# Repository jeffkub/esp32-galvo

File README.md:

# esp32-galvo
Laser galvo controller board using the ESP32.

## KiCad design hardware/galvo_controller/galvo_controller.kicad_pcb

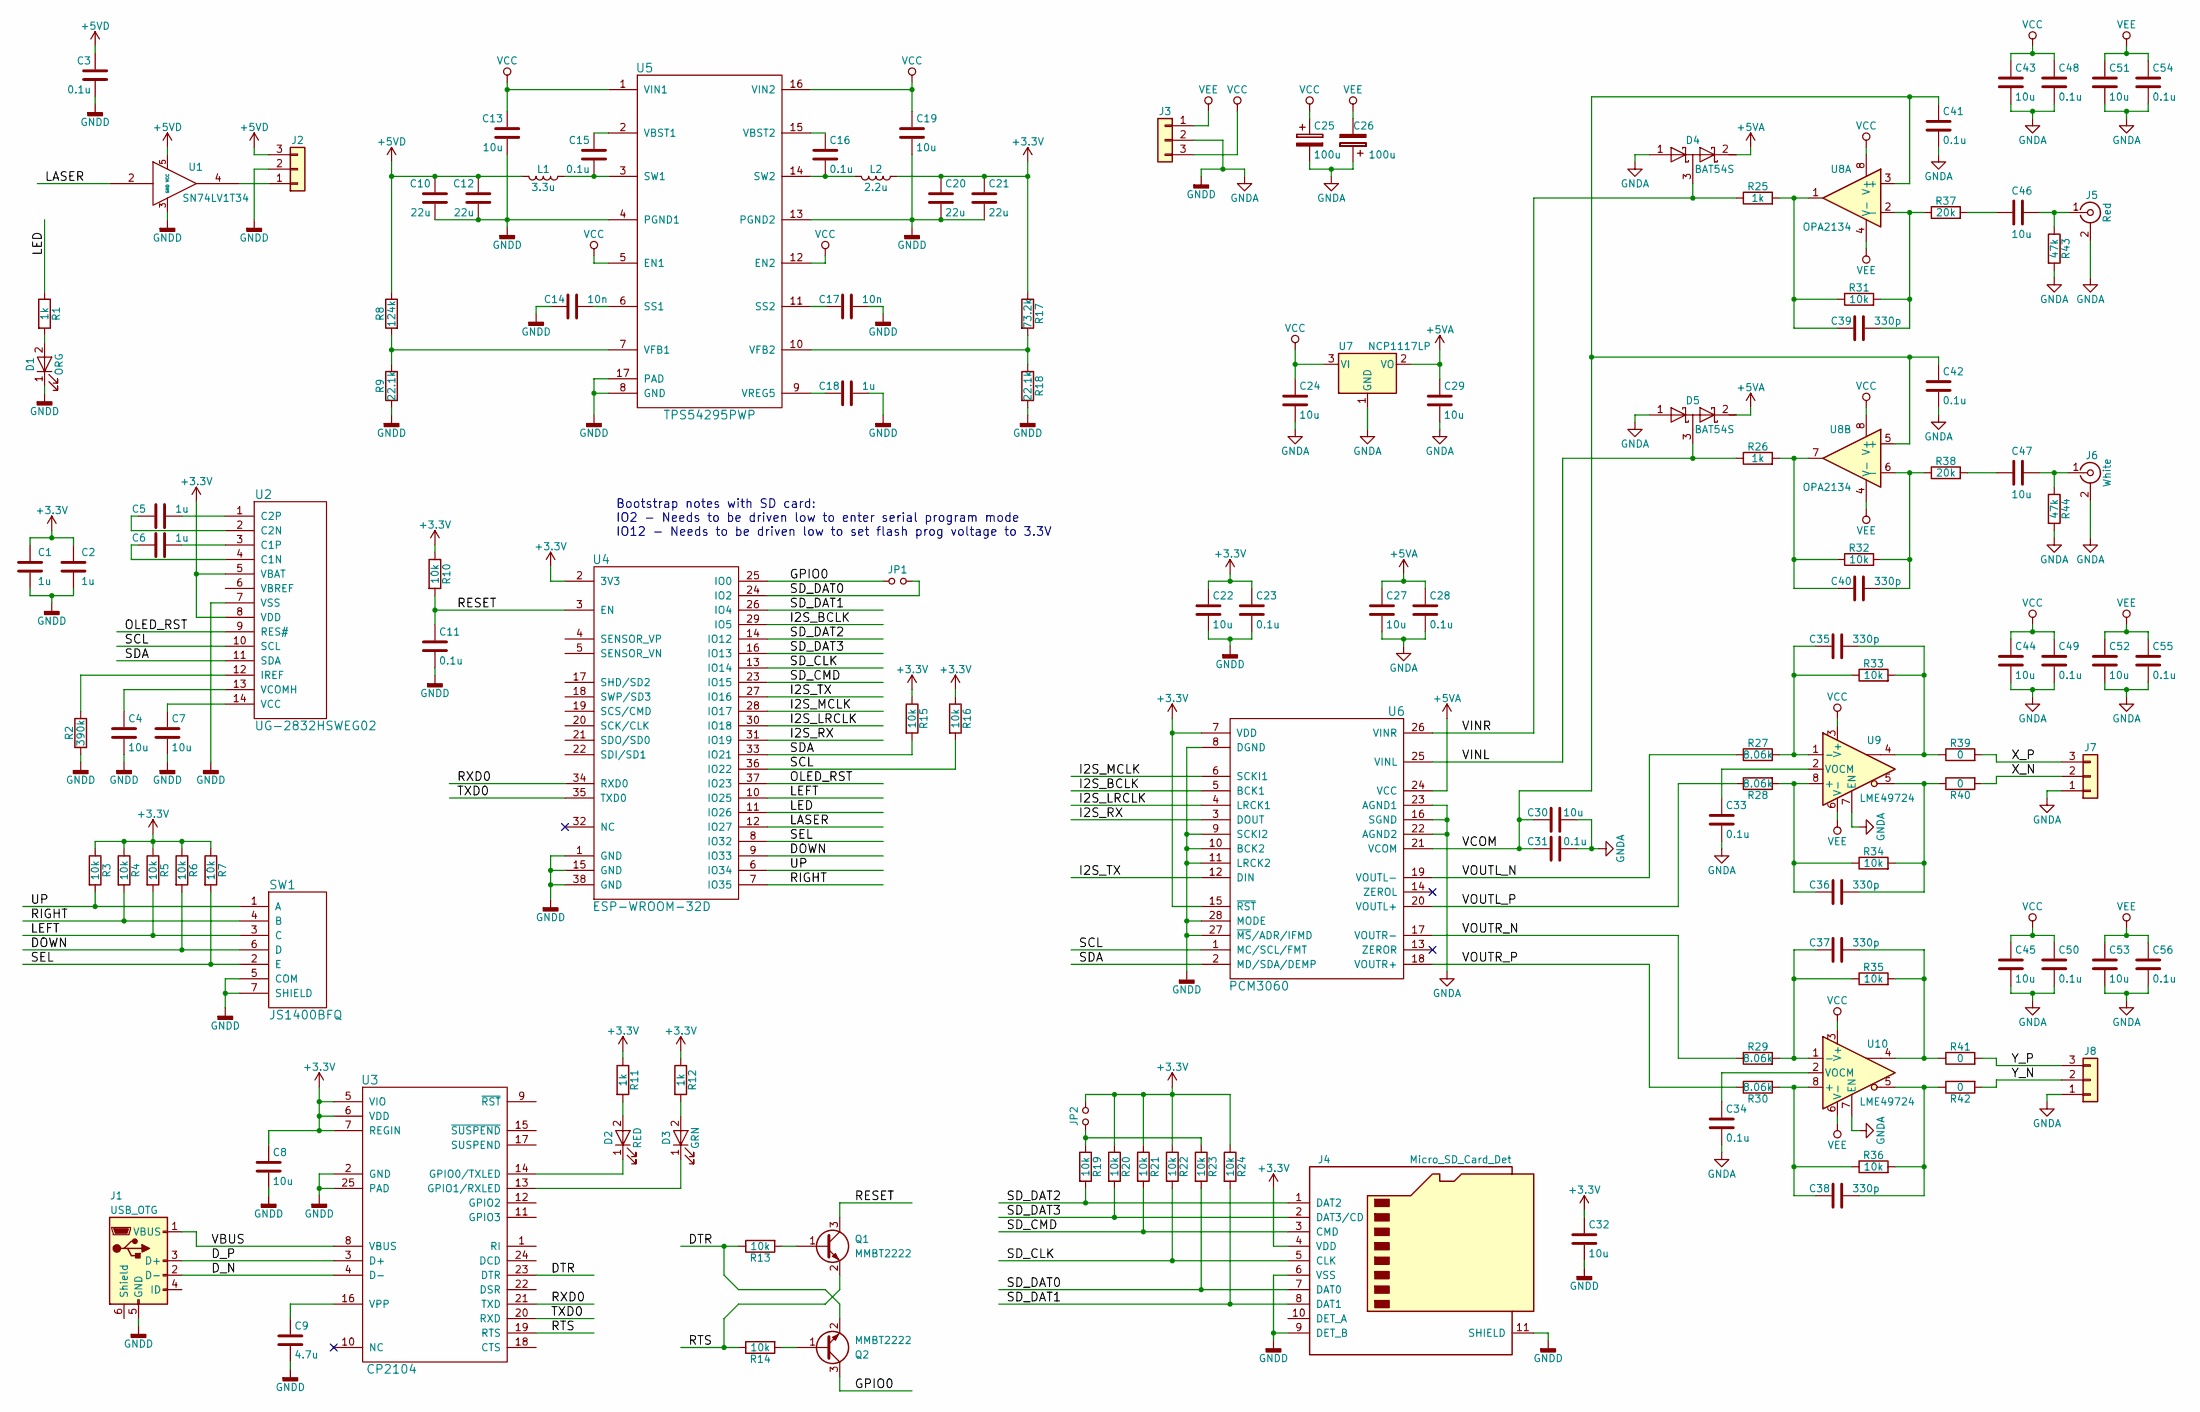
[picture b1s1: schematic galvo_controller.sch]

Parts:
C1, C2, C5, C6, C18: 1u; C_0805; Part 490-1691-1-ND
C3, C11, C15, C16, C23, C28, C31, C33, C34, C41, C42, C48, C49, C50, C54, C55, C56: 0.1u; C_0603; Part 490-9691-1-ND
C4, C7, C8, C13, C19, C22, C24, C27, C29, C30, C32, C43, C44, C45, C46, C47, C51, C52, C53: 10u; C_0805; Part 490-5523-1-ND
C9: 4.7u; C_0805; Part 490-5422-1-ND
C10, C12, C20, C21: 22u; C_1206; Part 490-6509-1-ND
C14, C17: 10n; C_0603; Part 490-9734-1-ND
C25, C26: 100u; CP_Elec_6.3x7.7; Part PCE3951CT-ND
C35, C36, C37, C38, C39, C40: 330p; C_0603; Part 490-11460-1-ND
D1: ORG; D_0603; Part 160-1434-1-ND
D2: RED; D_0603; Part 160-1447-1-ND
D3: GRN; D_0603; Part 160-1435-1-ND
D4, D5: BAT54S; SOT-23; Part BAT54S-FDICT-ND
J1: USB_OTG; 10118192; Part 609-4613-1-ND
J2, J7, J8: Conn_01x03; JST_XH_B03B-XH-A_03x2.50mm_Straight; Part 455-2248-ND
J3: Conn_01x03; Molex_KK-6410-03_03x2.54mm_Straight; Part WM4201-ND
J4: Micro_SD_Card_Det; 503182-1853; Part WM9750CT-ND
J5: Red; RCJ-01x; Part CP-1401-ND
J6: White; RCJ-01x; Part CP-1402-ND
JP1, JP2: Jumper_NO_Small; Pin_Header_Straight_1x02_Pitch2.54mm; Part 3M9457-02-ND
L1: 3.3u; CLF7045-D; Part 445-9554-1-ND
L2: 2.2u; CLF7045-D; Part 445-9553-1-ND
Q1, Q2: MMBT2222; SOT-23; Part MMBT2222ALT3GOSCT-ND
R1, R11, R12, R25, R26: 1k; R_0603; Part 311-1.00KHRCT-ND
R2: 390k; R_0603; Part 311-390KHRCT-ND
R3, R4, R5, R6, R7, R10, R13, R14, R15, R16, R19, R20, R21, R22, R23, R24, R31, R32, R33, R34, R35, R36: 10k; R_0603; Part 311-10.0KHRCT-ND
R8: 124k; R_0603; Part 311-124KHRCT-ND
R9, R18: 22.1k; R_0603; Part 311-22.1KHRCT-ND
R17: 73.2k; R_0603; Part 311-73.2KHRCT-ND
R27, R28, R29, R30: 8.06k; R_0603; Part 311-8.06KHRCT-ND
R37, R38: 20k; R_0603; Part 311-20.0KHRCT-ND
R39, R40, R41, R42: 0; R_0603; Part 311-0.0GRCT-ND
R43, R44: 47k; R_0603; Part 311-47.0KHRCT-ND
SW1: JS1400BFQ; Part 612-JS1400BFQ
U1: SN74LV1T34; SOT-23-5; Part 296-37176-1-ND
U2: UG-2832HSWEG02; Part UG-2832HSWEG02
U3: CP2104; QFN-24-1EP_4x4mm_Pitch0.5mm; Part 336-2008-5-ND
U4: ESP-WROOM-32D; ESP32-WROOM; Part 1528-1801-ND
U5: TPS54295PWP; HTSSOP-16-1EP_4.4x5mm_Pitch0.65mm_ThermalVias; Part 296-29960-1-ND
U6: PCM3060
U7: NCP1117LP; SOT-223-3_TabPin2; Part NCP1117LPST50T3GOSCT-ND
U8: OPA2134; SOIC-8_3.9x4.9mm_Pitch1.27mm; Part 296-22024-1-ND
U9, U10: LME49724; SOIC-8-1EP_3.9x4.9mm_Pitch1.27mm; Part 296-37390-1-ND

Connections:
+3V3: C1.2, C2.2, C8.1, C20.1, C21.1, C22.1, C23.1, C32.1, J4.4 (VDD), JP2.2, L2.1, R3.1, R4.1, R5.1, R6.1, R7.1, R10.1, R11.1, R12.1, R15.1, R16.1, R17.1, R20.1, R21.1, R22.1, R24.1, U2.5 (VBAT), U2.8 (VDD), U3.5 (VIO), U3.6 (VDD), U3.7 (REGIN), U4.2 (3V3), U6.7 (VDD), U6.15 (~RST)
+5VA: C27.1, C28.1, C29.1, D4.2 (K), D5.2 (K), U6.24 (VCC), U7.2 (VO)
+5VD: C3.1, C10.1, C12.1, J2.3, L1.2, R8.1, U1.5 (VCC)
/DOWN: R6.2, SW1.6 (D), U4.9 (IO33)
/DTR: Q2.2 (E), R13.1, U3.23 (DTR)
/D_N: J1.2 (D-), U3.4 (D-)
/D_P: J1.3 (D+), U3.3 (D+)
/GPIO0: JP1.1, Q2.3 (C), U4.25 (IO0)
/I2S_BCLK: U4.29 (IO5), U6.5 (BCK1)
/I2S_LRCLK: U4.30 (IO18), U6.4 (LRCK1)
/I2S_MCLK: U4.28 (IO17), U6.6 (SCKI1)
/I2S_RX: U4.31 (IO19), U6.3 (DOUT)
/I2S_TX: U4.27 (IO16), U6.12 (DIN)
/LASER: U1.2, U4.12 (IO27)
/LED: R1.1, U4.11 (IO26)
/LEFT: R5.2, SW1.3 (C), U4.10 (IO25)
/OLED_RST: U2.9 (RES#), U4.37 (IO23)
/RESET: C11.1, Q1.3 (C), R10.2, U4.3 (EN)
/RIGHT: R4.2, SW1.4 (B), U4.7 (IO35)
/RTS: Q1.2 (E), R14.1, U3.19 (RTS)
/RXD0: U3.21 (TXD), U4.34 (RXD0)
/SCL: R16.2, U2.10 (SCL), U4.36 (IO22), U6.1 (MC/SCL/FMT)
/SDA: R15.2, U2.11 (SDA), U4.33 (IO21), U6.2 (MD/SDA/DEMP)
/SD_CLK: J4.5 (CLK), R22.2, U4.13 (IO14)
/SD_CMD: J4.3 (CMD), R21.2, U4.23 (IO15)
/SD_DAT0: J4.7 (DAT0), JP1.2, R23.2, U4.24 (IO2)
/SD_DAT1: J4.8 (DAT1), R24.2, U4.26 (IO4)
/SD_DAT2: J4.1 (DAT2), R19.2, U4.14 (IO12)
/SD_DAT3: J4.2 (DAT3/CD), R20.2, U4.16 (IO13)
/SEL: R7.2, SW1.2 (E), U4.8 (IO32)
/TXD0: U3.20 (RXD), U4.35 (TXD0)
/UP: R3.2, SW1.1 (A), U4.6 (IO34)
/VBUS: J1.1 (VBUS), U3.8 (VBUS)
/VCOM: C30.2, C31.2, C41.1, C42.1, U6.21 (VCOM), U8.3 (+), U8.5 (+)
/VINL: D5.3 (common), R26.1, U6.25 (VINL)
/VINR: D4.3 (common), R25.1, U6.26 (VINR)
/VOUTL_N: R27.1, U6.19 (VOUTL-)
/VOUTL_P: R28.1, U6.20 (VOUTL+)
/VOUTR_N: R29.1, U6.17 (VOUTR-)
/VOUTR_P: R30.1, U6.18 (VOUTR+)
/X_N: J7.2, R40.2
/X_P: J7.3, R39.2
/Y_N: J8.2, R42.2
/Y_P: J8.3, R41.2
GNDA: C1.1, C2.1, C3.2, C4.2, C7.2, C8.2, C9.2, C10.2, C11.2, C12.2, C13.2, C14.2, C17.1, C18.1, C19.2, C20.2, C21.2, C22.2, C23.2, C24.2, C25.2, C26.1, C27.2, C28.2, C29.2, C30.1, C31.1, C32.2, C33.2, C34.2, C41.2, C42.2, C43.2, C44.2, C45.2, C48.2, C49.2, C50.2, C51.2, C52.2, C53.2, C54.2, C55.2, C56.2, D1.1 (K), D4.1 (A), D5.1 (A), J1.5 (GND), J2.2, J3.2, J4.6 (VSS), J4.9 (DET_B), J4.11 (SHIELD), J5.2 (Ext), J6.2 (Ext), J7.1, J8.1, R2.2, R9.2, R18.2, R43.2, R44.2, SW1.5 (COM), SW1.7 (SHIELD), U1.3 (GND), U2.7 (VSS), U3.2 (GND), U3.25 (PAD), U4.1 (GND), U4.15 (GND), U4.38 (GND), U5.4 (PGND1), U5.8 (GND), U5.13 (PGND2), U5.17 (PAD), U6.8 (DGND), U6.9 (SCKI2), U6.10 (BCK2), U6.11 (LRCK2), U6.16 (SGND), U6.22 (AGND2), U6.23 (AGND1), U6.27 (~MS~/ADR/IFMD), U6.28 (MODE), U7.1 (GND), U9.7 (EN), U10.7 (EN)
unnamed: C4.1, U2.13 (VCOMH)
unnamed: C5.1, U2.1 (C2P)
unnamed: C5.2, U2.2 (C2N)
unnamed: C6.1, U2.3 (C1P)
unnamed: C6.2, U2.4 (C1N)
unnamed: C7.1, U2.14 (VCC)
unnamed: C9.1, U3.16 (VPP)
unnamed: C14.1, U5.6 (SS1)
unnamed: C15.1, U5.2 (VBST1)
unnamed: C15.2, L1.1, U5.3 (SW1)
unnamed: C16.1, U5.15 (VBST2)
unnamed: C16.2, L2.2, U5.14 (SW2)
unnamed: C17.2, U5.11 (SS2)
unnamed: C18.2, U5.9 (VREG5)
unnamed: C33.1, U9.2 (VOCM)
unnamed: C34.1, U10.2 (VOCM)
unnamed: C35.1, R33.2, R39.1, U9.4
unnamed: C35.2, R27.2, R33.1, U9.1 (-)
unnamed: C36.1, R34.2, R40.1, U9.5
unnamed: C36.2, R28.2, R34.1, U9.8 (+)
unnamed: C37.1, R35.2, R41.1, U10.4
unnamed: C37.2, R29.2, R35.1, U10.1 (-)
unnamed: C38.1, R36.2, R42.1, U10.5
unnamed: C38.2, R30.2, R36.1, U10.8 (+)
unnamed: C39.1, R31.2, R37.1, U8.2 (-)
unnamed: C39.2, R25.2, R31.1, U8.1
unnamed: C40.1, R32.2, R38.1, U8.6 (-)
unnamed: C40.2, R26.2, R32.1, U8.7
unnamed: C46.1, J5.1 (In), R43.1
unnamed: C46.2, R37.2
unnamed: C47.1, J6.1 (In), R44.1
unnamed: C47.2, R38.2
unnamed: D1.2 (A), R1.2
unnamed: D2.1 (K), U3.14 (GPIO0/TXLED)
unnamed: D2.2 (A), R11.2
unnamed: D3.1 (K), U3.13 (GPIO1/RXLED)
unnamed: D3.2 (A), R12.2
unnamed: J2.1, U1.4
unnamed: JP2.1, R19.1, R23.1
unnamed: Q1.1 (B), R13.2
unnamed: Q2.1 (B), R14.2
unnamed: R2.1, U2.12 (IREF)
unnamed: R8.2, R9.1, U5.7 (VFB1)
unnamed: R17.2, R18.1, U5.10 (VFB2)
VCC: C13.1, C19.1, C24.1, C25.1, C43.1, C44.1, C45.1, C48.1, C49.1, C50.1, J3.3, U5.1 (VIN1), U5.5 (EN1), U5.12 (EN2), U5.16 (VIN2), U7.3 (VI), U8.8 (V+), U9.3 (V+), U10.3 (V+)
VEE: C26.2, C51.1, C52.1, C53.1, C54.1, C55.1, C56.1, J3.1, U8.4 (V-), U9.6 (V-), U9.9 (V-), U10.6 (V-), U10.9 (V-)

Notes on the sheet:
Bootstrap notes with SD card: IO2 - Needs to be driven low to enter serial program mode IO12 - Needs to be driven low to set flash prog voltage to 3.3V

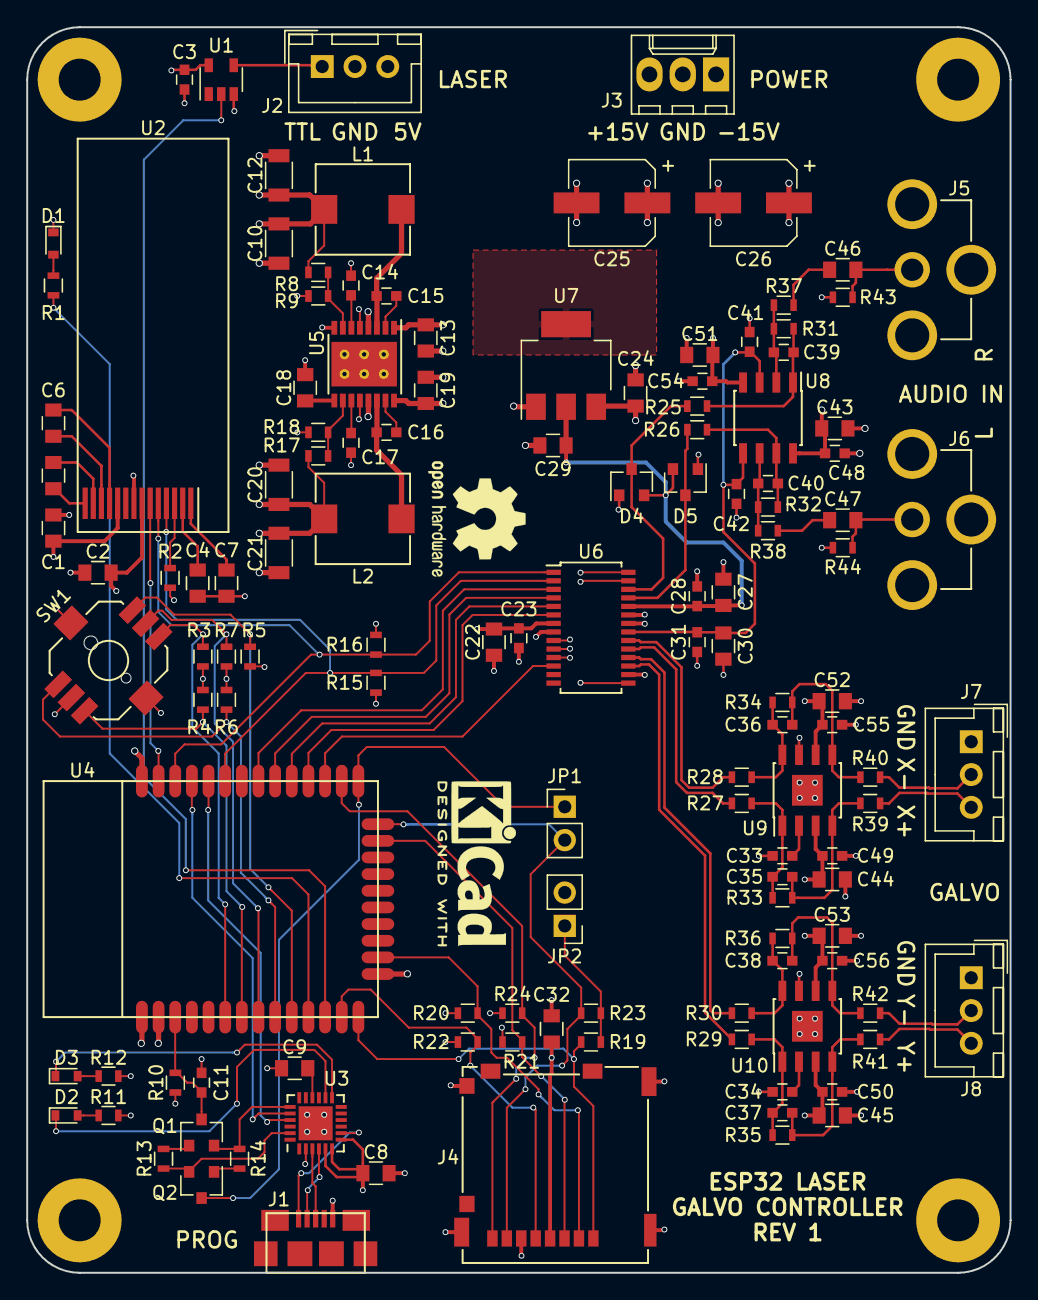
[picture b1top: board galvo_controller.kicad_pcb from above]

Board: 4 copper layers, 75.0 x 95.0 mm, 130 parts (0 on the bottom side), 91 nets.

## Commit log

2018-03-08 Renamed kicad project
2018-03-08 Created pdf
2018-03-08 Working on schematic
2018-03-10 Switched to ESP32 microcontroller
2018-03-10 Using switching regulator for 3.3V and 5V rails
2018-03-10 Updated PDF
2018-03-10 Changed to single buck DC DC converter
2018-03-11 Working on footprints
2018-03-11 Finished BOM, exported to layout
2018-03-11 Working on component placement
2018-03-12 Working on layout
2018-03-12 Switched to logic buffer for laser enable
2018-03-13 Tweaked SD card pullup jumpers
2018-03-14 Added oled display
2018-03-14 Adding directional switch
2018-03-14 Added oled display (reverted from commit 7e9d64baadf71845b197ee83ec8b18551d687449)
2018-03-14 Restored footprints/ symbols for OLED and nav switch
2018-03-14 Swapped input L/R channels
2018-03-14 Created symbol and footprint for directional switch
2018-03-15 Added OLED and nav switch
2018-03-15 Re-annotated schematic
2018-03-16 Finished routing board
2018-03-16 Adjusted oled footprint
2018-03-16 Adding silkscreen text
2018-03-17 Cleaned up reference designators, finalizing layout
2018-03-17 Added kicad-libs as a git submodule
2018-03-17 Moved footprints and symbols into git submodule
2018-03-17 Changed power connector. Added symbols
2018-03-17 Fixed connector pinouts, working on silkscreen layers
2018-03-17 Minor PCB tweaks
2018-03-17 Exported gerbers
2018-03-18 Tweaked solder mask and paste settings
2018-03-18 Fixed missing part number on BOM
2018-03-18 Added 3d render image
2018-03-18 Updated 3d render image
2018-03-18 Created firmware project
2018-03-18 Created blinky example
